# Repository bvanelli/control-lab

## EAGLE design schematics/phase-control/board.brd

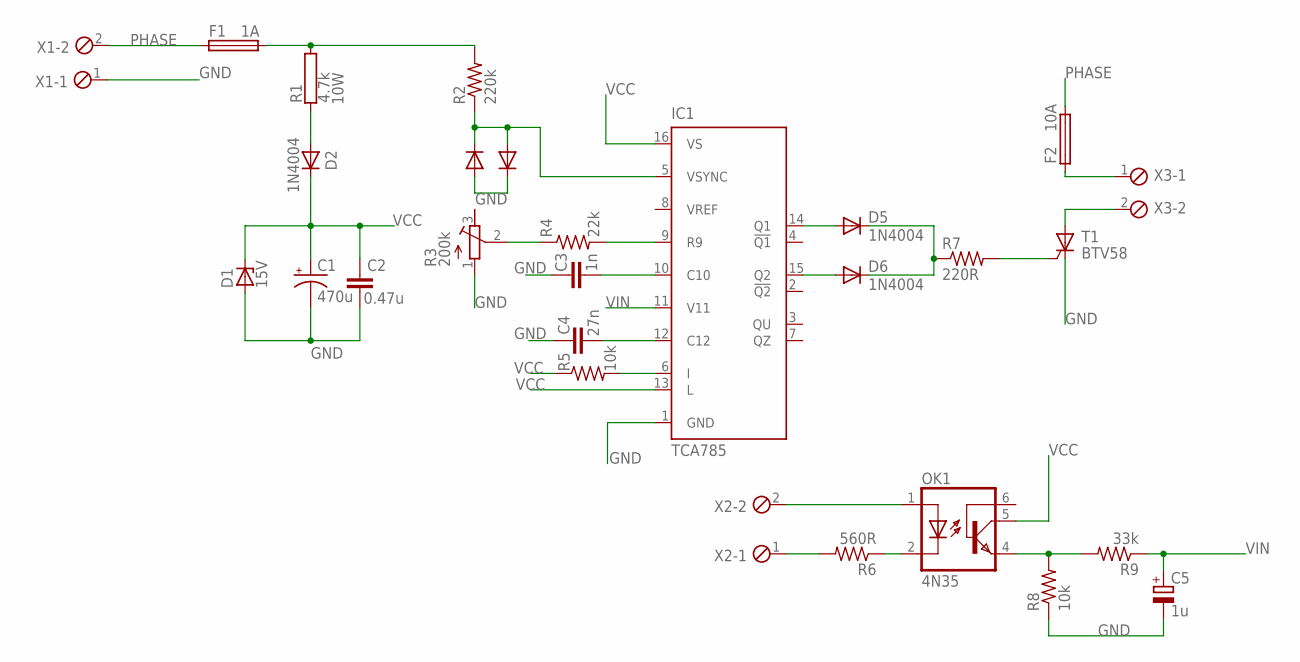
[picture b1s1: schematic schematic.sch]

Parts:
C1: 470u; E3,5-8
C2: 0.47u; C025-025X050
C3: 1n; C025-025X050
C4: 27n; C025-025X050
C5: 1u; E2,5-6E
D1: 15V; F126Z12
D2, D3, D4, D5, D6: 1N4004; DO41-10
F1: 1A; SH25
F2: 10A; SH25
IC1: TCA785; DIL16
OK1: 4N35; DIL06
R1: 4.7k; AC10
R2: 220k; 0207/10
R3: 200k; RTRIM64W
R4: 22k; 0207/10
R5: 10k; 0207/15
R6: 560R; 0204/7
R7: 220R; 0207/15
R8: 10k; 0207/12
R9: 33k; 0207/12
T1: BTV58; TO220CS
X1, X2, X3: MPT2; 2POL254

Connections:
GND: C1.-, C2.1, C3.1, C4.1, C5.-, D1.A, D3.A, D4.C, IC1.1 (GND), R3.1 (A), R8.1, T1.C, X1.1
unnamed: D2.A, R1.1
unnamed: R3.2 (S), R4.1
unnamed: D3.C, D4.A, IC1.5 (VSYNC), R2.1
unnamed: IC1.9 (R9), R4.2
unnamed: C4.2, IC1.12 (C12)
unnamed: C3.2, IC1.10 (C10)
unnamed: IC1.6 (I), R5.2
unnamed: D6.A, IC1.15 (Q2)
unnamed: D5.A, IC1.14 (Q1)
unnamed: D5.C, D6.C, R7.1
unnamed: R7.2, T1.G
unnamed: F2.1, X3.1
unnamed: F1.2, R1.2, R2.2
unnamed: T1.A, X3.2
unnamed: OK1.4 (EMI), R8.2, R9.2
unnamed: R6.2, X2.1
unnamed: OK1.2 (C), R6.1
unnamed: OK1.1 (A), X2.2
PHASE: F1.1, F2.2, X1.2
VCC: C1.+, C2.2, D1.C, D2.C, IC1.13 (L), IC1.16 (VS), OK1.5 (COL), R5.1
VIN: C5.+, IC1.11 (V11), R9.1

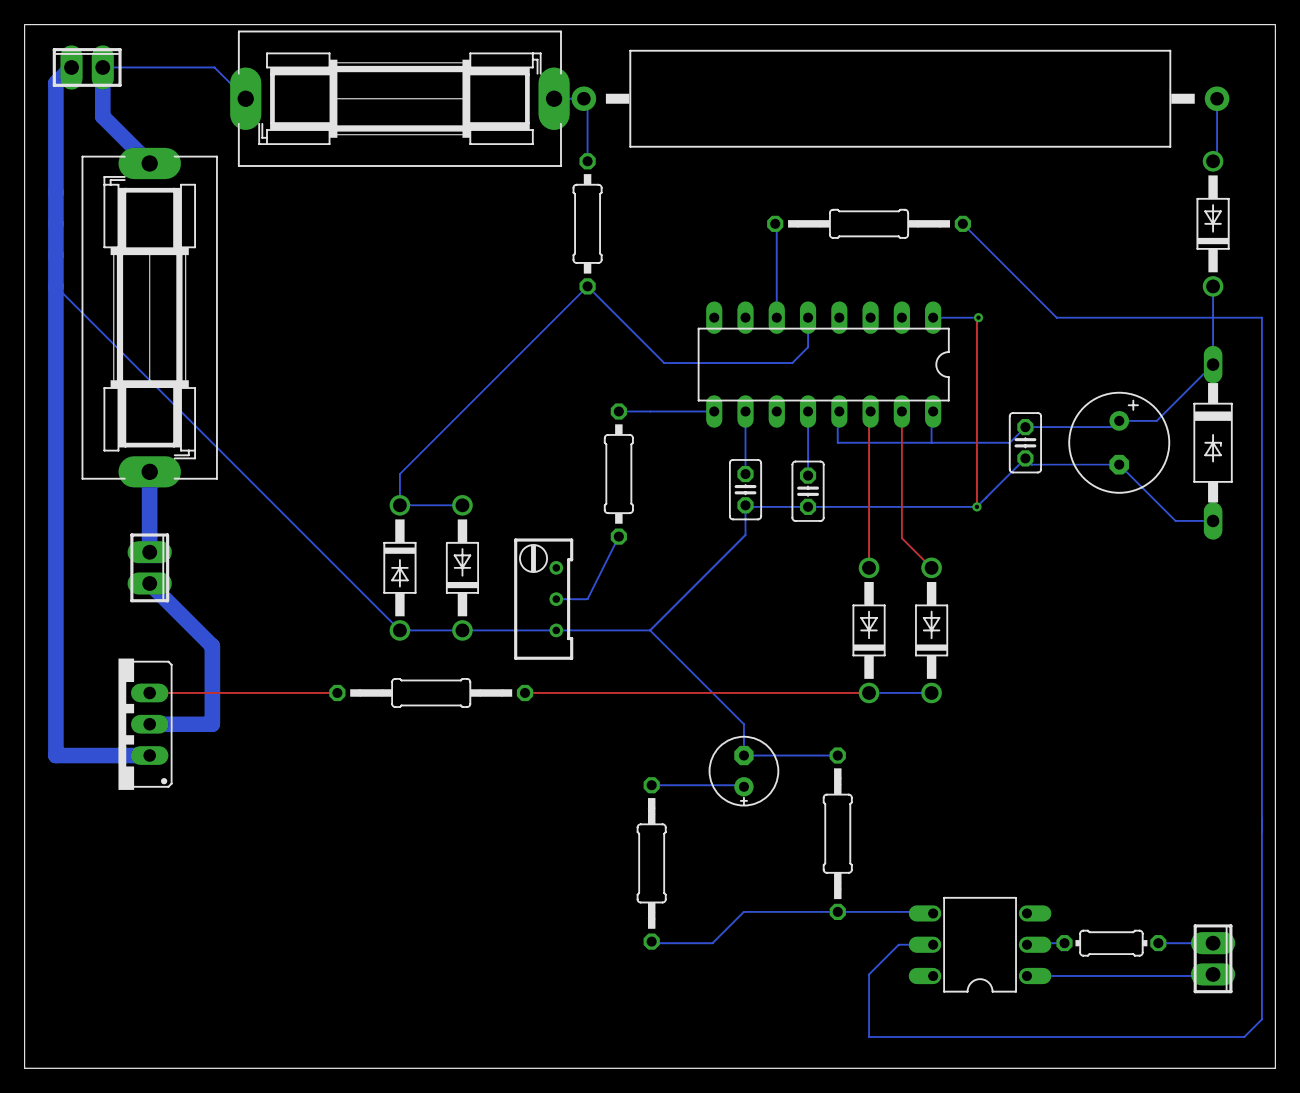
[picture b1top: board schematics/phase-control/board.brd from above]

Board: 3 copper layers, 101.6 x 84.8 mm, 28 parts (0 on the bottom side), 22 nets.

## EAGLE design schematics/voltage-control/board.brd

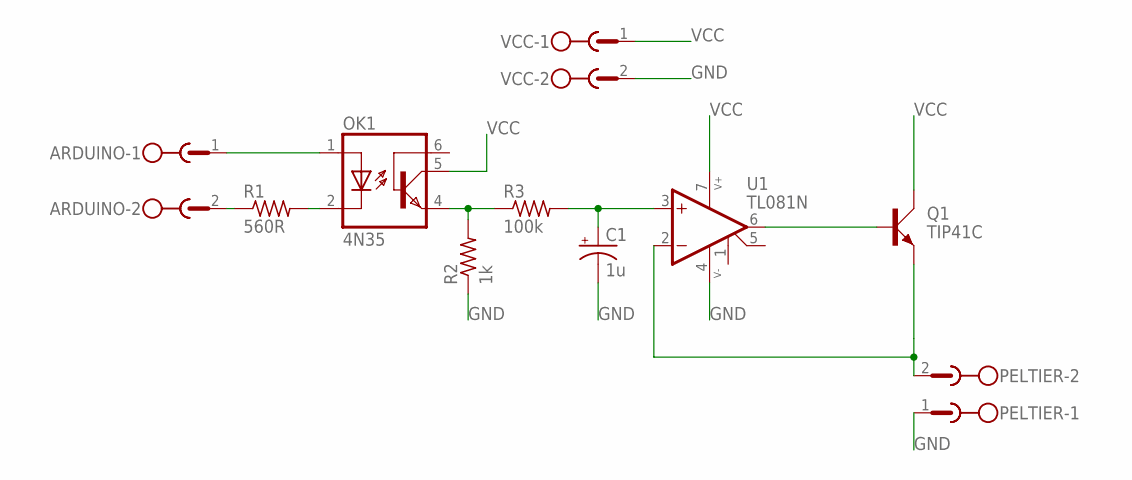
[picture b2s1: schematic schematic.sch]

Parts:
ARDUINO: MSTBV2
C1: 1u; E2,5-7
OK1: 4N35; DIL06
PELTIER: MST2V; MSTBV2
Q1: TIP41C; TO220AV
R1: 560R; 0207/10
R2: 1k; 0207/10
R3: 100k; 0207/10
U1: TL081N; DIL08
VCC: MSTBV2

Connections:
GND: C1.-, PELTIER.1, R2.1, U1.4 (V-), VCC.2
unnamed: ARDUINO.2, R1.1
unnamed: OK1.2 (C), R1.2
unnamed: ARDUINO.1, OK1.1 (A)
unnamed: OK1.4 (EMI), R2.2, R3.1
unnamed: C1.+, R3.2, U1.3 (+IN)
unnamed: Q1.B, U1.6 (OUT)
unnamed: PELTIER.2, Q1.E, U1.2 (-IN)
VCC: OK1.5 (COL), Q1.C, U1.7 (V+), VCC.1

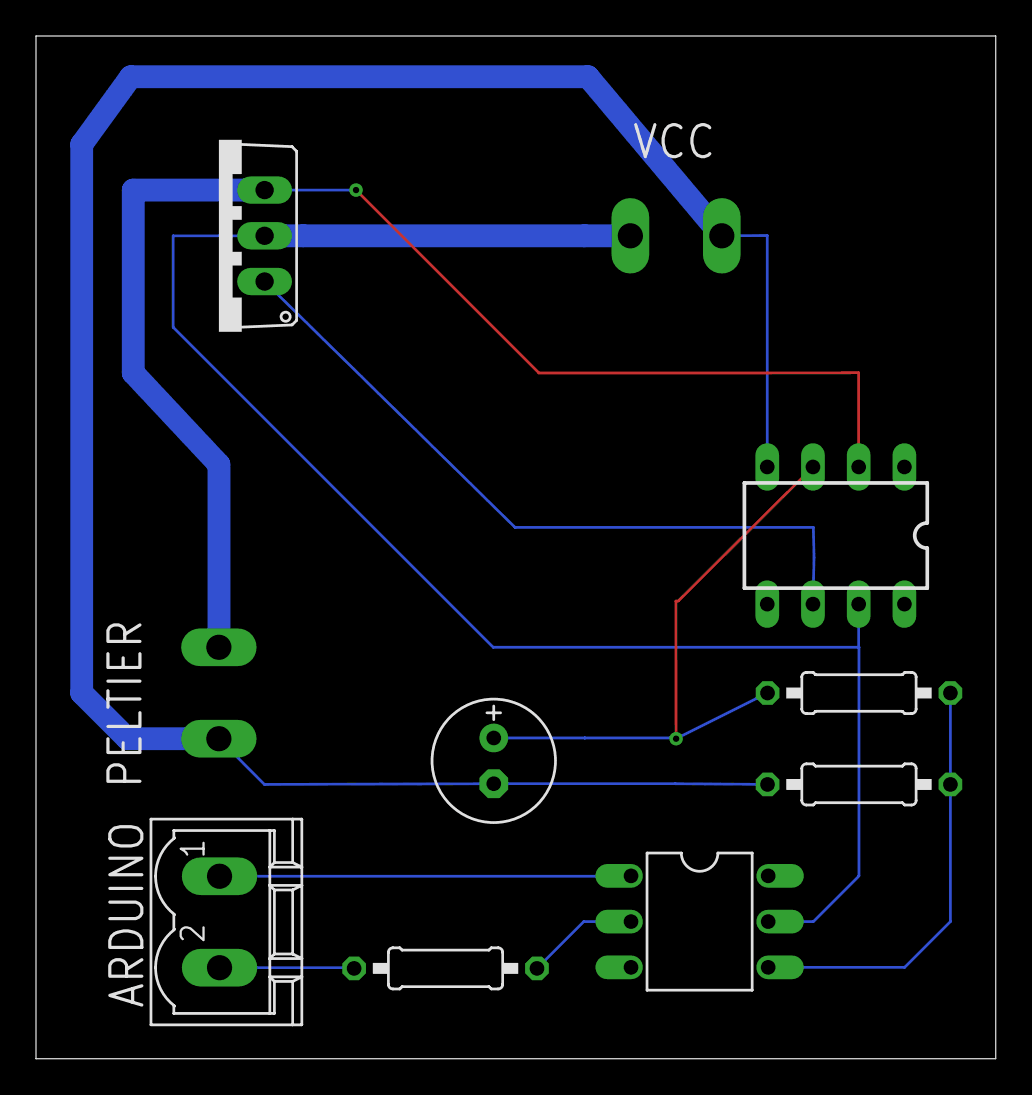
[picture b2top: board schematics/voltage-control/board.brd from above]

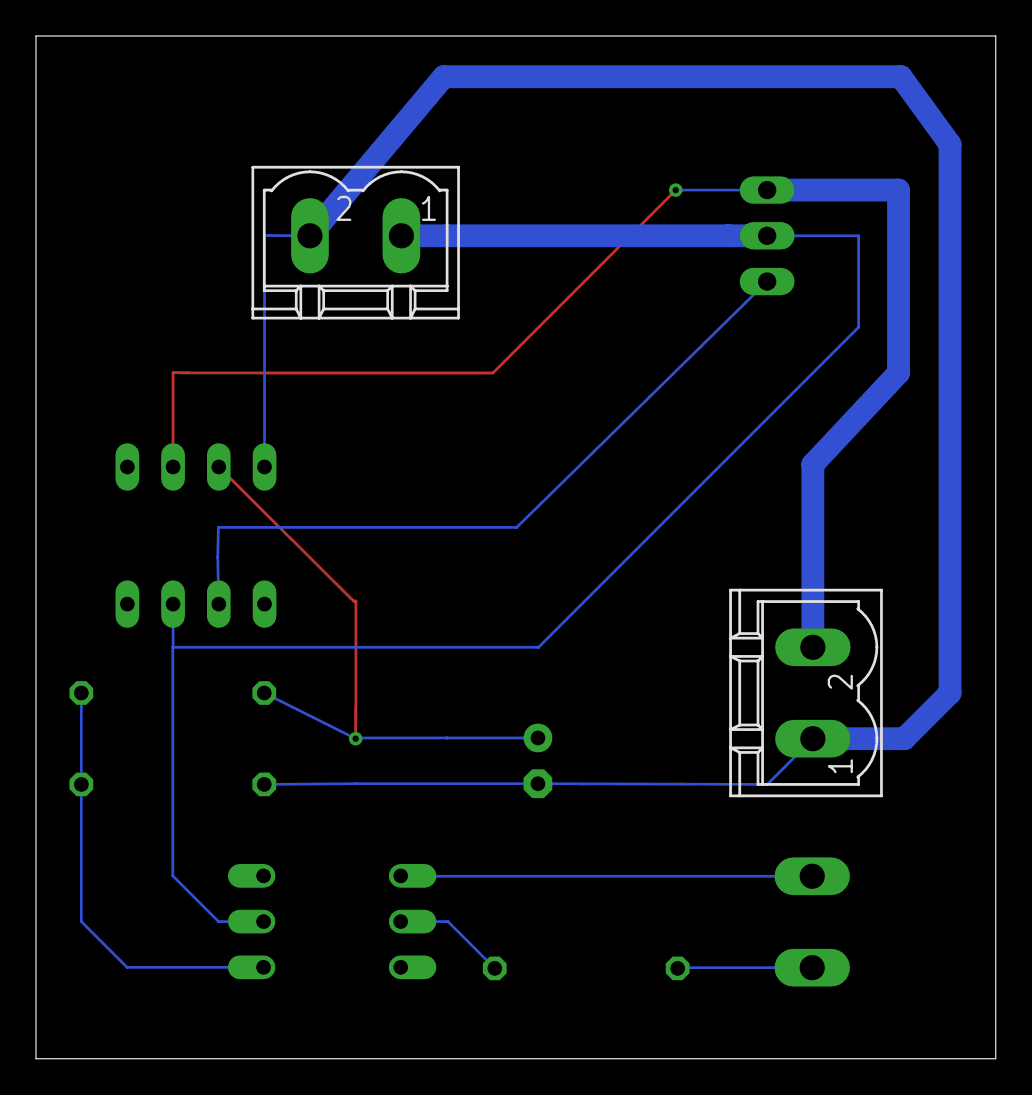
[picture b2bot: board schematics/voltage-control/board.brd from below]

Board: 2 copper layers, 53.3 x 56.8 mm, 10 parts (2 on the bottom side), 9 nets.

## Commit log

2018-03-30 Added main skeleton for documentation.
2018-05-09 Full revision of site to make everything look great.
2018-05-09 Fixed paths from global to relative.
2018-05-09 Finally fixed permalinks. Should be good now
2018-05-09 Small fixes to links
2018-05-12 More documentation and some images.
2018-05-12 Some fixes and updating fa to version 5.
2018-05-12 Some more changes.
2018-05-15 Temporary fix for TOC. TODO: permament fix for toc?
2018-05-17 I can't believe I spent 4 hours to perfect a menu... Finally done
2018-05-22 Simulink
2018-05-26 Finally working scripts.
2018-05-26 Main sketch on how to build phase-controller
2018-05-29 Great improvements to both plants.
2018-05-29 Added schematics
2018-05-29 Added MATLAB files.
2018-05-30 Added more information about temperature sensor.
2018-06-02 Added some bootstrap files and additions to experiments.
2018-06-02 Some minor refinements.
2018-06-02 Added matlab model for first system.
2018-06-02 Suppress warnings about pygments.
2018-06-04 Added docker wrapup to deploy faster.
2018-06-06 Added pictures of circuits.
2018-06-07 Added download link.
2018-06-07 Minor refinements.
2018-06-07 Final picture to matlab documentation.
2018-06-10 Much writing, such changes.
2018-06-10 Added step response data for exp3.
2018-06-10 Added both models and redirected target to _blank.
2018-06-10 Added model2 for peltier system.
2018-06-12 Added fixes to all exps and added exp2 and exp4.
2018-06-12 You can know include tex support with ease using jekyll.
2018-06-13 Changed model to correct one.
2018-06-13 Added correct models.
2018-06-13 It should be all right.

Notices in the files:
parts and their libraries:
op-amp: Copyright (C) 2006 by Bob Starr
